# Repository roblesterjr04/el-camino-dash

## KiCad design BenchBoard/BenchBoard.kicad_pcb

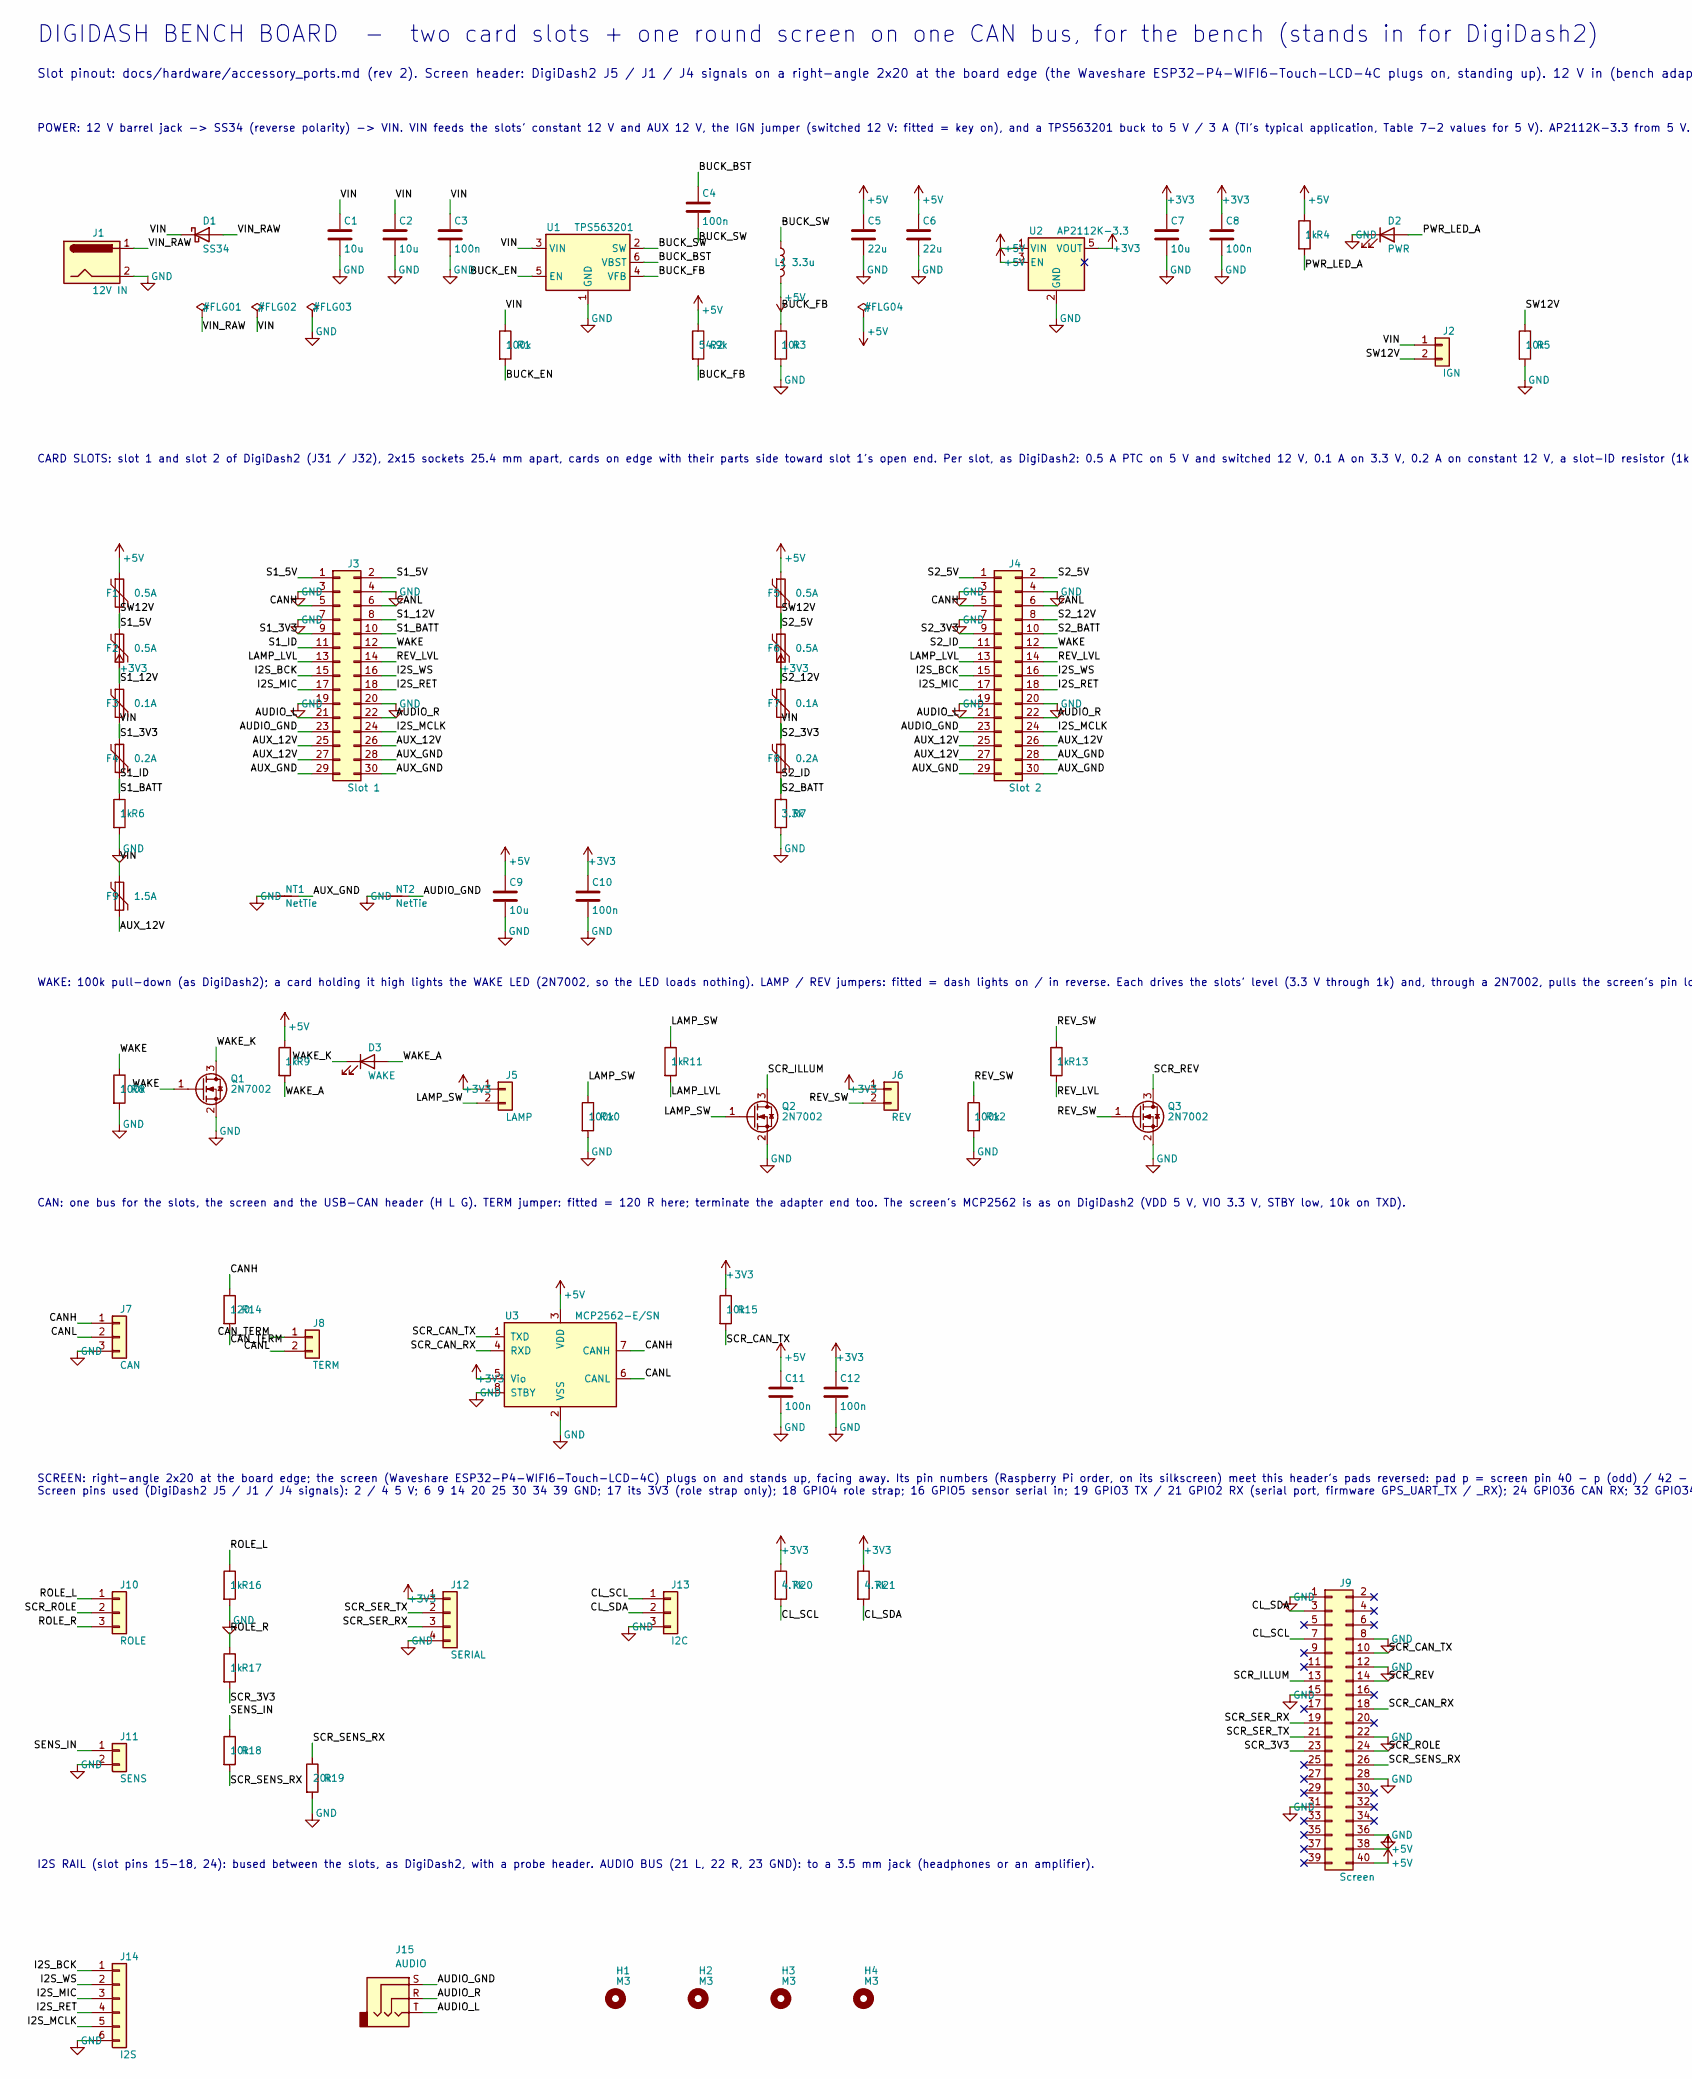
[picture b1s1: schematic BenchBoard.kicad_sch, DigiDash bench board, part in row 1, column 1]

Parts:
C1, C2: 10u; C_1206_3216Metric
C3, C4, C8, C10, C11, C12: 100n; C_0603_1608Metric
C5, C6: 22u; C_0805_2012Metric
C7, C9: 10u; C_0805_2012Metric
D1: SS34; D_SMA
D2: PWR; LED_0603_1608Metric
D3: WAKE; LED_0603_1608Metric
F1, F2, F5, F6: 0.5A; Fuse_1206_3216Metric
F3, F7: 0.1A; Fuse_1206_3216Metric
F4, F8: 0.2A; Fuse_1206_3216Metric
F9: 1.5A; Fuse_1812_4532Metric
H1, H2, H3, H4: M3; MountingHole_3.2mm_M3
J1: 12V IN; BarrelJack_CUI_PJ-063AH_Horizontal
J2: IGN; PinHeader_1x02_P2.54mm_Vertical
J3: Slot 1; PinSocket_2x15_P2.54mm_Vertical
J4: Slot 2; PinSocket_2x15_P2.54mm_Vertical
J5: LAMP; PinHeader_1x02_P2.54mm_Vertical
J6: REV; PinHeader_1x02_P2.54mm_Vertical
J7: CAN; PinHeader_1x03_P2.54mm_Vertical
J8: TERM; PinHeader_1x02_P2.54mm_Vertical
J9: Screen; PinHeader_2x20_P2.54mm_Horizontal
J10: ROLE; PinHeader_1x03_P2.54mm_Vertical
J11: SENS; PinHeader_1x02_P2.54mm_Vertical
J12: SERIAL; JST_PH_S4B-PH-K_1x04_P2.00mm_Horizontal
J13: I2C; PinHeader_1x03_P2.54mm_Vertical
J14: I2S; PinHeader_1x06_P2.54mm_Vertical
J15: AUDIO; Jack_3.5mm_CUI_SJ1-3523N_Horizontal
L1: 3.3u; L_Bourns_SRN6045TA
NT1, NT2: NetTie; NetTie-2_SMD_Pad0.5mm
Q1, Q2, Q3: 2N7002; SOT-23
R1, R8, R10, R12: 100k; R_0603_1608Metric
R2: 54.9k; R_0603_1608Metric
R3, R5, R15, R18: 10k; R_0603_1608Metric
R4, R6, R9, R11, R13, R16, R17: 1k; R_0603_1608Metric
R7: 3.3k; R_0603_1608Metric
R14: 120; R_0603_1608Metric
R19: 20k; R_0603_1608Metric
R20, R21: 4.7k; R_0603_1608Metric
U1: TPS563201; SOT-23-6
U2: AP2112K-3.3; SOT-23-5
U3: MCP2562-E/SN; SOIC-8_3.9x4.9mm_P1.27mm

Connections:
+3V3: C7.1, C8.1, C10.1, C12.1, F3.1, F7.1, J5.1, J6.1, J12.1, R15.1, R20.1, R21.1, U2.5 (VOUT), U3.5 (Vio)
+5V: C5.1, C6.1, C9.1, C11.1, F1.1, F5.1, J9.38, J9.40, L1.2, R2.1, R4.1, R9.1, U2.1 (VIN), U2.3 (EN), U3.3 (VDD)
/AUDIO_GND: J3.23, J4.23, J15.S, NT2.2
/AUDIO_L: J3.21, J4.21, J15.T
/AUDIO_R: J3.22, J4.22, J15.R
/AUX_12V: F9.2, J3.25, J3.26, J3.27, J4.25, J4.26, J4.27
/AUX_GND: J3.28, J3.29, J3.30, J4.28, J4.29, J4.30, NT1.2
/BUCK_BST: C4.1, U1.6 (VBST)
/BUCK_EN: R1.2, U1.5 (EN)
/BUCK_FB: R2.2, R3.1, U1.4 (VFB)
/BUCK_SW: C4.2, L1.1, U1.2 (SW)
/CANH: J3.5, J4.5, J7.1, R14.1, U3.7 (CANH)
/CANL: J3.6, J4.6, J7.2, J8.2, U3.6 (CANL)
/CAN_TERM: J8.1, R14.2
/CL_SCL: J9.7, J13.1, R20.2
/CL_SDA: J9.3, J13.2, R21.2
/I2S_BCK: J3.15, J4.15, J14.1
/I2S_MCLK: J3.24, J4.24, J14.5
/I2S_MIC: J3.17, J4.17, J14.3
/I2S_RET: J3.18, J4.18, J14.4
/I2S_WS: J3.16, J4.16, J14.2
/LAMP_LVL: J3.13, J4.13, R11.2
/LAMP_SW: J5.2, Q2.1 (G), R10.1, R11.1
/PWR_LED_A: D2.2 (A), R4.2
/REV_LVL: J3.14, J4.14, R13.2
/REV_SW: J6.2, Q3.1 (G), R12.1, R13.1
/ROLE_L: J10.1, R16.1
/ROLE_R: J10.3, R17.1
/S1_3V3: F3.2, J3.9
/S1_5V: F1.2, J3.1, J3.2
/S1_12V: F2.2, J3.8
/S1_BATT: F4.2, J3.10
/S1_ID: J3.11, R6.1
/S2_3V3: F7.2, J4.9
/S2_5V: F5.2, J4.1, J4.2
/S2_12V: F6.2, J4.8
/S2_BATT: F8.2, J4.10
/S2_ID: J4.11, R7.1
/SCR_3V3: J9.23, R17.2
/SCR_CAN_RX: J9.18, U3.4 (RXD)
/SCR_CAN_TX: J9.10, R15.2, U3.1 (TXD)
/SCR_ILLUM: J9.13, Q2.3 (D)
/SCR_REV: J9.14, Q3.3 (D)
/SCR_ROLE: J9.24, J10.2
/SCR_SENS_RX: J9.26, R18.2, R19.1
/SCR_SER_RX: J9.19, J12.3
/SCR_SER_TX: J9.21, J12.2
/SENS_IN: J11.1, R18.1
/SW12V: F2.1, F6.1, J2.2, R5.1
/VIN: C1.1, C2.1, C3.1, D1.1 (K), F4.1, F8.1, F9.1, J2.1, R1.1, U1.3 (VIN)
/VIN_RAW: D1.2 (A), J1.1
/WAKE: J3.12, J4.12, Q1.1 (G), R8.1
/WAKE_A: D3.2 (A), R9.2
/WAKE_K: D3.1 (K), Q1.3 (D)
GND: C1.2, C2.2, C3.2, C5.2, C6.2, C7.2, C8.2, C9.2, C10.2, C11.2, C12.2, D2.1 (K), J1.2, J3.3, J3.4, J3.7, J3.19, J3.20, J4.3, J4.4, J4.7, J4.19, J4.20, J7.3, J9.1, J9.8, J9.12, J9.15, J9.22, J9.28, J9.31, J9.36, J11.2, J12.4, J13.3, J14.6, NT1.1, NT2.1, Q1.2 (S), Q2.2 (S), Q3.2 (S), R3.2, R5.2, R6.2, R7.2, R8.2, R10.2, R12.2, R16.2, R19.2, U1.1 (GND), U2.2 (GND), U3.2 (VSS), U3.8 (STBY)

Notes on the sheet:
DIGIDASH BENCH BOARD - two card slots + one round screen on one CAN bus, for the bench (stands in for DigiDash2)
Slot pinout: docs/hardware/accessory_ports.md (rev 2). Screen header: DigiDash2 J5 / J1 / J4 signals on a right-angle 2x20 at the board edge (the Waveshare ESP32-P4-WIFI6-Touch-LCD-4C plugs on, standing up). 12 V in (bench adapter, 17 V max).
POWER: 12 V barrel jack -> SS34 (reverse polarity) -> VIN. VIN feeds the slots' constant 12 V and AUX 12 V, the IGN jumper (switched 12 V: fitted = key on), and a TPS563201 buck to 5 V / 3 A (TI's typical application, Table 7-2 values for 5 V). AP2112K-3.3 from 5 V.
CARD SLOTS: slot 1 and slot 2 of DigiDash2 (J31 / J32), 2x15 sockets 25.4 mm apart, cards on edge with their parts side toward slot 1's open end. Per slot, as DigiDash2: 0.5 A PTC on 5 V and switched 12 V, 0.1 A on 3.3 V, 0.2 A on constant 12 V, a slot-ID resistor (1k slot 1, 3.3k slot 2: nodes 0x1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
WAKE: 100k pull-down (as DigiDash2); a card holding it high lights the WAKE LED (2N7002, so the LED loads nothing). LAMP / REV jumpers: fitted = dash lights on / in reverse. Each drives the slots' level (3.3 V through 1k) and, through a 2N7002, pulls the screen's pin low (GPIO24 illumination: low =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
CAN: one bus for the slots, the screen and the USB-CAN header (H L G). TERM jumper: fitted = 120 R here; terminate the adapter end too. The screen's MCP2562 is as on DigiDash2 (VDD 5 V, VIO 3.3 V, STBY low, 10k on TXD).
SCREEN: right-angle 2x20 at the board edge; the screen (Waveshare ESP32-P4-WIFI6-Touch-LCD-4C) plugs on and stands up, facing away. Its pin numbers (Raspberry Pi order, on its silkscreen) meet this header's pads reversed: pad p = screen pin 40 - p (odd) / 42 - p (even). Screen pins used (DigiDash2 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
I2S RAIL (slot pins 15-18, 24): bused between the slots, as DigiDash2, with a probe header. AUDIO BUS (21 L, 22 R, 23 GND): to a 3.5 mm jack (headphones or an amplifier).

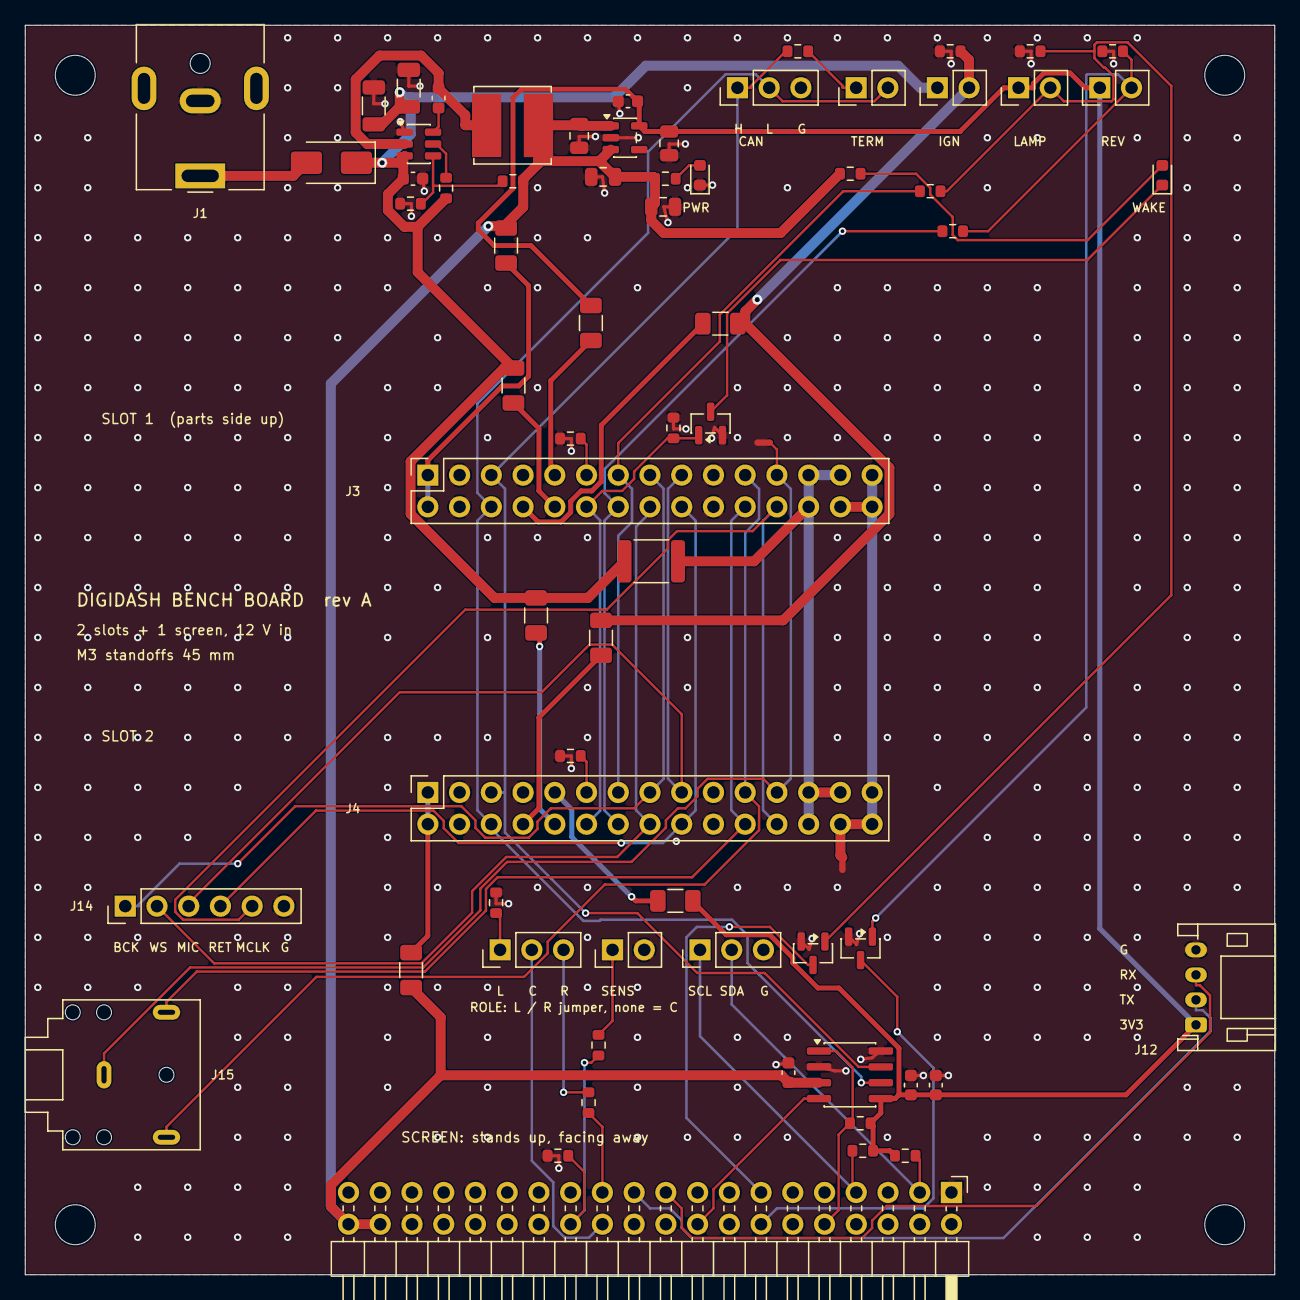
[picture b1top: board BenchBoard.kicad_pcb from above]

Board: 2 copper layers, 100.0 x 100.0 mm, 73 parts (0 on the bottom side), 55 nets.

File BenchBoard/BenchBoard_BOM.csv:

Qty,Designators,Manufacturer part,Description,Package,Type,Side,Notes
1,U1,Texas Instruments TPS563201DDCR,"TI TPS563201DDCR: 3 A synchronous buck, 4.5-17 V in, SOT-23-6. 5 V out",SOT-23-6,SMD,Top,
1,U2,Diodes Inc AP2112K-3.3TRG1,"Diodes AP2112K-3.3TRG1: 600 mA LDO, 3.3 V, EN tied to VIN",SOT-23-5,SMD,Top,
1,U3,Microchip MCP2562-E/SN,Microchip MCP2562-E/SN: the screen's CAN transceiver (as DigiDash2 U9),SOIC-8_3.9x4.9mm_P1.27mm,SMD,Top,
1,L1,Bourns SRN6045TA-3R3Y,"3.3 uH, 6 x 6 mm, Isat > 4 A (Bourns SRN6045TA-3R3M). TI Table 7-2: 3.3 uH for 5 V",L_Bourns_SRN6045TA,SMD,Top,Isat 7.8 A
1,D1,Vishay SS34-E3/57T,"Reverse-polarity diode, 3 A Schottky (SS34, SMA)",D_SMA,SMD,Top,Reverse-polarity diode
1,D2,Lite-On LTST-C191KGKT,Power LED: 5 V present,0603,SMD,Top,
1,D3,Lite-On LTST-C191KSKT,WAKE LED: a card holds WAKE high,0603,SMD,Top,
1,Q1,"Nexperia 2N7002,215",WAKE LED driver,SOT-23,SMD,Top,
1,Q2,"Nexperia 2N7002,215","Screen illumination input (GPIO24, active low = dim)",SOT-23,SMD,Top,
1,Q3,"Nexperia 2N7002,215","Screen reverse trigger (GPIO25, active low)",SOT-23,SMD,Top,
1,J1,CUI Devices PJ-063AH,"12 V in: 5.5 / 2.1 mm barrel jack, centre positive (CUI PJ-063AH)",BarrelJack_CUI_PJ-063AH_Horizontal,THT,Top,"Bench adapter: 12 V, 3 A, centre positive (17 V max: the buck's limit)"
1,J2,Sullins PRPC002SAAN-RC,"IGN jumper: fitted = key on (switched 12 V to the slots, pin 8); removed = key off",PinHeader_1x02_P2.54mm_Vertical,THT,Top,
1,J3,Sullins PPTC152LFBN-RC,"Card slot 1: 2x15 female socket, 2.54 mm, vertical (the DigiDash2 slot pinout)",PinSocket_2x15_P2.54mm_Vertical,THT,Top,Same socket as DigiDash2's slots
1,J4,Sullins PPTC152LFBN-RC,"Card slot 2: 2x15 female socket, 2.54 mm, vertical (the DigiDash2 slot pinout)",PinSocket_2x15_P2.54mm_Vertical,THT,Top,Same socket as DigiDash2's slots
1,J5,Sullins PRPC002SAAN-RC,LAMP jumper: fitted = dash lights on,PinHeader_1x02_P2.54mm_Vertical,THT,Top,
1,J6,Sullins PRPC002SAAN-RC,REV jumper: fitted = in reverse,PinHeader_1x02_P2.54mm_Vertical,THT,Top,
1,J7,Sullins PRPC003SAAN-RC,"USB-CAN adapter: 1 CANH, 2 CANL, 3 GND",PinHeader_1x03_P2.54mm_Vertical,THT,Top,
1,J8,Sullins PRPC002SAAN-RC,TERM jumper: fitted = 120 R across the bus,PinHeader_1x02_P2.54mm_Vertical,THT,Top,
1,J9,Sullins PRPC020DBAN-M71RC,"Screen: 2x20 right-angle male header, 2.54 mm, at the board edge (pad p = screen pin 40 - p odd / 42 - p even)",PinHeader_2x20_P2.54mm_Horizontal,THT,Top,"Right angle, on the bottom edge, pins pointing off the board (the screen plugs onto them)"
1,J10,Sullins PRPC003SAAN-RC,"ROLE jumper: 1-2 = left, 2-3 = right, none = center (the DigiDash2 strap on GPIO4)",PinHeader_1x03_P2.54mm_Vertical,THT,Top,
1,J11,Sullins PRPC002SAAN-RC,"Sensor serial in: a jumper wire from the sensor card's J8 (pin 2 TX, pin 1 GND); 5 V logic",PinHeader_1x02_P2.54mm_Vertical,THT,Top,
1,J12,JST S4B-PH-K-S,"Serial port (GPS puck), JST PH 4 pin side entry, as DigiDash2 J6: 1 3V3, 2 TX out (screen GPIO3), 3 RX in (screen GPIO2), 4 GND",JST_PH_S4B-PH-K_1x04_P2.00mm_Horizontal,THT,Top,"Right edge, opening off the board"
1,J13,Sullins PRPC003SAAN-RC,"Cluster I2C (screen GPIO48 SCL, GPIO47 SDA): to a second screen or a probe",PinHeader_1x03_P2.54mm_Vertical,THT,Top,
1,J14,Sullins PRPC006SAAN-RC,"I2S rail probe: 1 BCK, 2 WS, 3 MIC, 4 RET, 5 MCLK, 6 GND",PinHeader_1x06_P2.54mm_Vertical,THT,Top,
1,J15,CUI Devices SJ1-3523N,"Audio bus out: 3.5 mm stereo jack (tip L, ring R, sleeve audio GND)",Jack_3.5mm_CUI_SJ1-3523N_Horizontal,THT,Top,"Left edge, opening off the board"
1,F1,Bourns MF-NSMF050-2,"Slot 1 5 V, 0.5 A hold",1206,SMD,Top,
1,F2,Littelfuse 1206L050/15YR,"Slot 1 switched 12 V, 0.5 A hold",1206,SMD,Top,
1,F3,Bourns MF-NSMF010-2,"Slot 1 3.3 V, 0.1 A hold",1206,SMD,Top,
1,F4,Bourns MF-NSMF020-2,"Slot 1 constant 12 V, 0.2 A hold",1206,SMD,Top,
1,F5,Bourns MF-NSMF050-2,"Slot 2 5 V, 0.5 A hold",1206,SMD,Top,
1,F6,Littelfuse 1206L050/15YR,"Slot 2 switched 12 V, 0.5 A hold",1206,SMD,Top,
1,F7,Bourns MF-NSMF010-2,"Slot 2 3.3 V, 0.1 A hold",1206,SMD,Top,
1,F8,Bourns MF-NSMF020-2,"Slot 2 constant 12 V, 0.2 A hold",1206,SMD,Top,
1,F9,Bourns MF-MSMF150/24X-2,"AUX 12 V to both slots, 1.5 A hold (1812)",1812,SMD,Top,
4,R1 R8 R10 R12,Yageo RC0603FR-07100KL,"100k resistor, 1 %",0603,SMD,Top,
1,R2,Yageo RC0603FR-0754K9L,"54.9k: Feedback top (TI R1, 5 V: 0.768 x (1 + 54.9 / 10) = 4.98 V)",0603,SMD,Top,
4,R3 R5 R15 R18,Yageo RC0603FR-0710KL,"10k resistor, 1 %",0603,SMD,Top,
7,R4 R6 R9 R11 R13 R16 R17,Yageo RC0603FR-071KL,"1k resistor, 1 %",0603,SMD,Top,
1,R7,Yageo RC0603FR-073K3L,3.3k: Slot 2 ID (as DigiDash2: the card reads it with its own pull-up),0603,SMD,Top,
1,R14,Yageo RC0603FR-07120RL,"120: Bus termination, with the TERM jumper",0603,SMD,Top,
1,R19,Yageo RC0603FR-0720KL,20k: Sensor serial divider bottom: 5 V to 3.3 V,0603,SMD,Top,
2,R20 R21,Yageo RC0603FR-074K7L,"4.7k resistor, 1 %",0603,SMD,Top,
2,C1 C2,Samsung CL31A106KAHNNNE,10u capacitor,1206,SMD,Top,
6,C3 C4 C8 C10 C11 C12,Samsung CL10B104KB8NNNC,100n capacitor,0603,SMD,Top,
2,C5 C6,Samsung CL21A226MPQNNNE,22u capacitor,0805,SMD,Top,
2,C7 C9,Samsung CL21A106KPFNNNE,10u capacitor,0805,SMD,Top,
,,,"Plus 6 loose 2.54 mm jumper shunts (Sullins QPC02SXGN-RC), not placed: IGN, LAMP, REV, TERM, ROLE, spare",,,,
